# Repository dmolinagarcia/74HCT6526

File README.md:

>
> DISCLAIMER
> Everything you see here is the result of the work of an amateur hobbyist. I had no knowledge in any required field for this project when I started, so I offer no guarantee that, if you replicate my work, you may end burning up you Commodore, your fingertips, or your whole house.
> So far, no Commodore equipment (or fingertips, or whole house) have been permanently damaged in any way. But I can't promise to keep it that way.
>

# 74HCT6526 
The 74HCT6526 is a very amateur attempt at building a MOS6526 replica using discrete logic. This repo is publicly shared just for educational purposes, and I can offer no guarantee on the correct behaviour of this implementation. So far, it's working great for me, but I can't promise anything.

# Current Status
As of v0.2.2, the 74HCT6526 is extremely cycle accurate when compared to a real 6526. Some VICE test still fail on edge cases, but it has been tested against multiple games with very satisfactory results. 

# History
Work on the 74HCT6526 began in the summer of 2018. I was so impressed by other attempts at replicating Commodore chips, that I wanted to give it myself a try. I chose the CIA, as it wasn't replicated back then, even though it seemed the simplest chip. I had no previous knowledge in electronics, only some lessons back in college more than 20 years ago.

> ###### Important note
> Please visit http://forum.6502.org/viewtopic.php?f=4&t=5593 for more information

# Versioning
74HCT6526 is released under the following versioning scheme:

> MAJOR.MINOR.REVISION

For a stack to work properly, is mandatory that all boards share the same MAJOR.MINOR versión. Any change than renders a board incompatible with the previous releases triggers a new MINOR version. If a version only includes fixes, but does not alter the buses, it's only a new revision. There may be some cases where boards with different MAJOR.MINOR version can actually work together, but this is not something I can guarantee or predict. A deep look at the schematics to understand the differences between releases is needed to actually confirm this.

Under the current scheme, I don't think I'll ever need a new MAJOR version, but it is nice to have it there, just in case.

# Upgrades
In the upgrades folder, there's a guide for each version/board pair, with instructions to upgrade the board up until the latest version. You'll see theres no file for the latest version (As there's no upgrade path for it).

Whenever a new release is published, upgrade path for the now second-oldest release will by published.

> WARNING! I offer no guarantee on anything on this project, but, specially on the upgrades part. 

# Manufacturing
All boards are tested against JLCPCB and PCBWAY capabilities. For PCBWAY, there is no increase in cost compared to the standard 4 layer board.

# Releases
* v0.1.0  First production run. Only includes B0 (DDR and PORTs)
* v0.1.0a First production run for B1. (TIMERA and CREGA)
* v0.1.1  Second production run for B1. Fixes TASTART issue. First B2 (TIMERB and CREGB) 
* v0.1.2  First production run for B3. (SDR and ICR)
* v0.2.0  First MINOR advance. B0+B1+B2+B3 tested and validated. 
* v0.2.1  Fixes for Reload under Underflow issue. 
* v0.2.2  First production run for B4 (TOD). It now passes test 01 and 02 in both NEW and OLD modes.

# Changelog
## [0.2.2 ] - 23-Jun-2023
* B0. Some HCT parts are changed to HC
* B1. Split TIMER into modules for improved readability
* B2. Split TIMER into modules for improved readability
* B3. Issue #12. Fixed all issues for test 02
* B3. Master Switch for Mode Change. (Old vs NEW)
* B3. Some HC parts are changed to HCT
* B4. Added TOD PCB and SCH
* All boards. Published upgrade procedures

## [0.2.1 ] - 26-Mar-2023
* All boards. Added pdfs for all schematic and pcbs for all versions for ease of access
* B1. Changes to Reload portion of TimerA pipeline to fix 01cmpold issue
* B2. Changes to Reload portion of TimerA pipeline to fix 01cmpold issue
* B3. Added switch to select OLD or NEW CIA

## [0.2.0 ] - 24-Jan-2023
* All boards. Removed TARUNMODE from the ControlBus
* All boards. Updated for JLCPCB and PCBWAY capabilities
* All boards. Minor aesthetic changes to schematics
* All boards. Updated PDFs on the release
* B1. Optimized CNT edge detector
* B2. Optimized CNT edge detector
* B3. Fixed FLAG edge detector in ICR
* B3. Fixed SDR input and output issues from v0.1.2 (not sending nor receiving)

## [0.1.2 ] - 01-Nov-2022 
* B3. First release. SDR and ICR
* B2. Updates for JLCPCB capabilities
* All boards. Schematic review. Added /RES capacitor to prevent false restarts

## [0.1.1 ] - 24-Aug-2022 
* B2. First release. 
* B1. Fixed additional cycle on forceload by removing second flipflop in the chain (rolled-back)
* B1. Added additionad dFF to Start before being fed into the timer
* B1. D and DZ moved to separate buses on schematic.
* B0. Routing optimized. D and DZ moved to separate buses on schematic. Silkscreen improved. 

## [0.1.0a] - 06-Jun-2022
* B1 with TimerA and Control Register A. Ready for production. 

## [0.1.0 ] - 19-Oct-2021
* Mounting holes pads were covered with soldermask. Soldermask removed and pads properly labeled.
* Silkscreen fixes
* Updated gerber files
* B0 with DDRs, PORTs, and bus interface

# Status updates
* June 23, 2023. v0.2.2 released. Adds TOD (B4) and fixes more NEW to OLD issues. Now passes tests 01 and 02.
* March 26, 2023. v0.2.1 released. Fixes a missing IRQ issue on reload while underflowing. It also adds a selector for OLD vs NEW cia in ICR
* January 24, 2023. v0.2.0 released. Fixes a potential problem on B1 and B2 with CNT edge detector. It also fixes some bugs on B3. A cleanup of schematic, PCBs and PDFs for all boards has been done. TARUNMODE is removed from controlbus as it is not needed. This triggers a new MINOR version
* November 01, 2022. v0.1.2 released. Includes B3 (SDR+ICR) and some minor tweaks to all boards
* August 24, 2022. v0.1.1 released. Fixes a bug in B1 (TASTART) and adds B2. Minor routing fixes to all boards
* June 06, 2022. v0.1.0a released. It adds B1 to v0.1.0
* October 19, 2021. v0.1.0 is released. It add B0 to v0.1.0
* September 12th, 2021. Repository is now public. B0 schematic is 100% done. PCB layout is 100% done. It's currently being reviewed before sending it into production

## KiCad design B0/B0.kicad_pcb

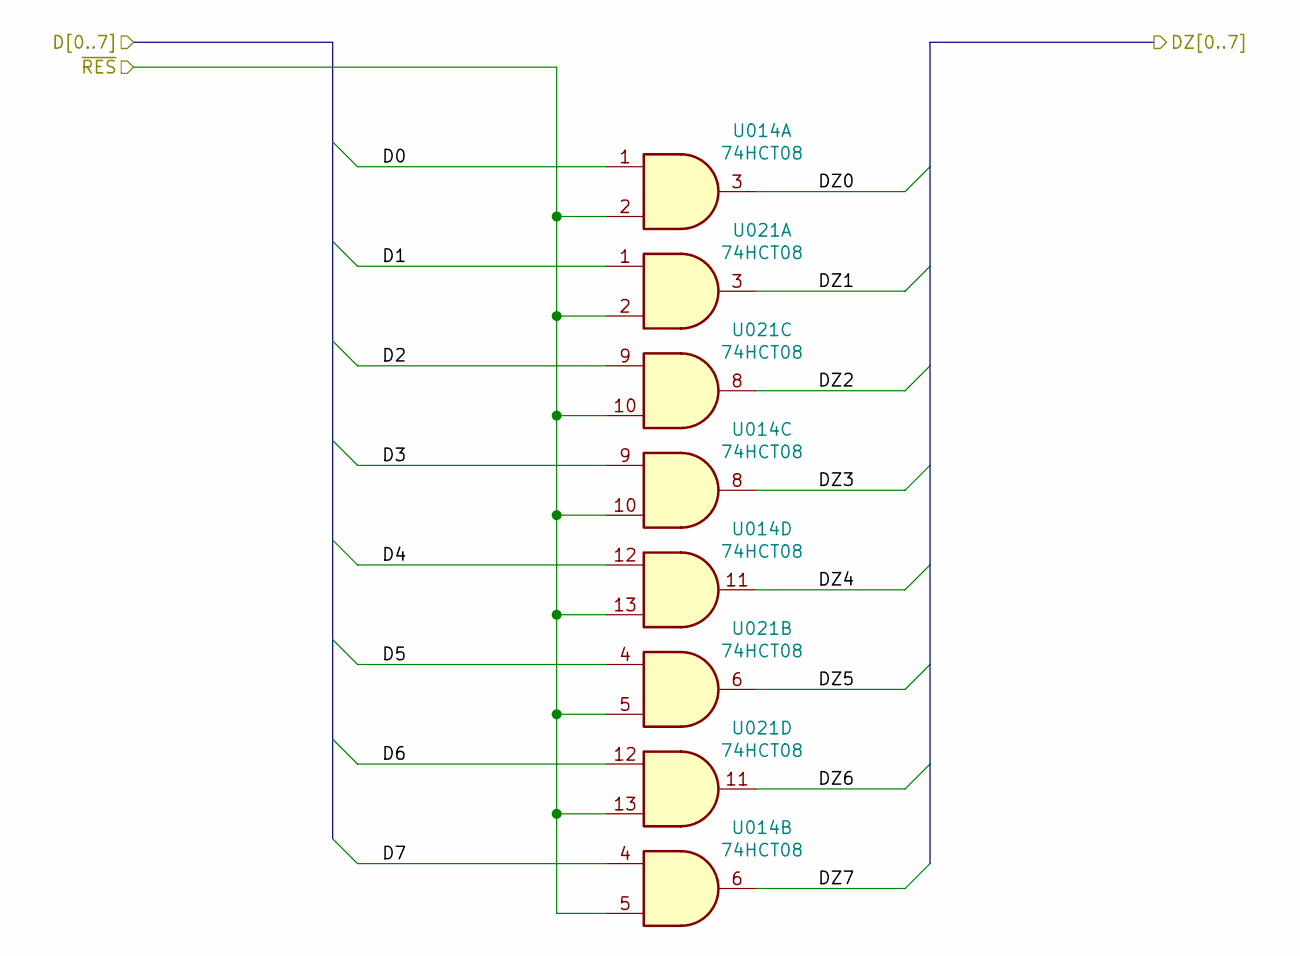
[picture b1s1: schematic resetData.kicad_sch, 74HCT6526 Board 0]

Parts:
U014, U021: 74HCT08; SO-14

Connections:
D0: U014.1; also elsewhere on the board
D1: U021.1; also elsewhere on the board
D2: U021.9; also elsewhere on the board
D3: U014.9; also elsewhere on the board
D4: U014.12; also elsewhere on the board
D5: U021.4; also elsewhere on the board
D6: U021.12; also elsewhere on the board
D7: U014.4; also elsewhere on the board
DZ0: U014.3; also elsewhere on the board
DZ1: U021.3; also elsewhere on the board
DZ2: U021.8; also elsewhere on the board
DZ3: U014.8; also elsewhere on the board
DZ4: U014.11; also elsewhere on the board
DZ5: U021.6; also elsewhere on the board
DZ6: U021.11; also elsewhere on the board
DZ7: U014.6; also elsewhere on the board
~RES: U014.2, U014.5, U014.10, U014.13, U021.2, U021.5, U021.10, U021.13; also elsewhere on the board

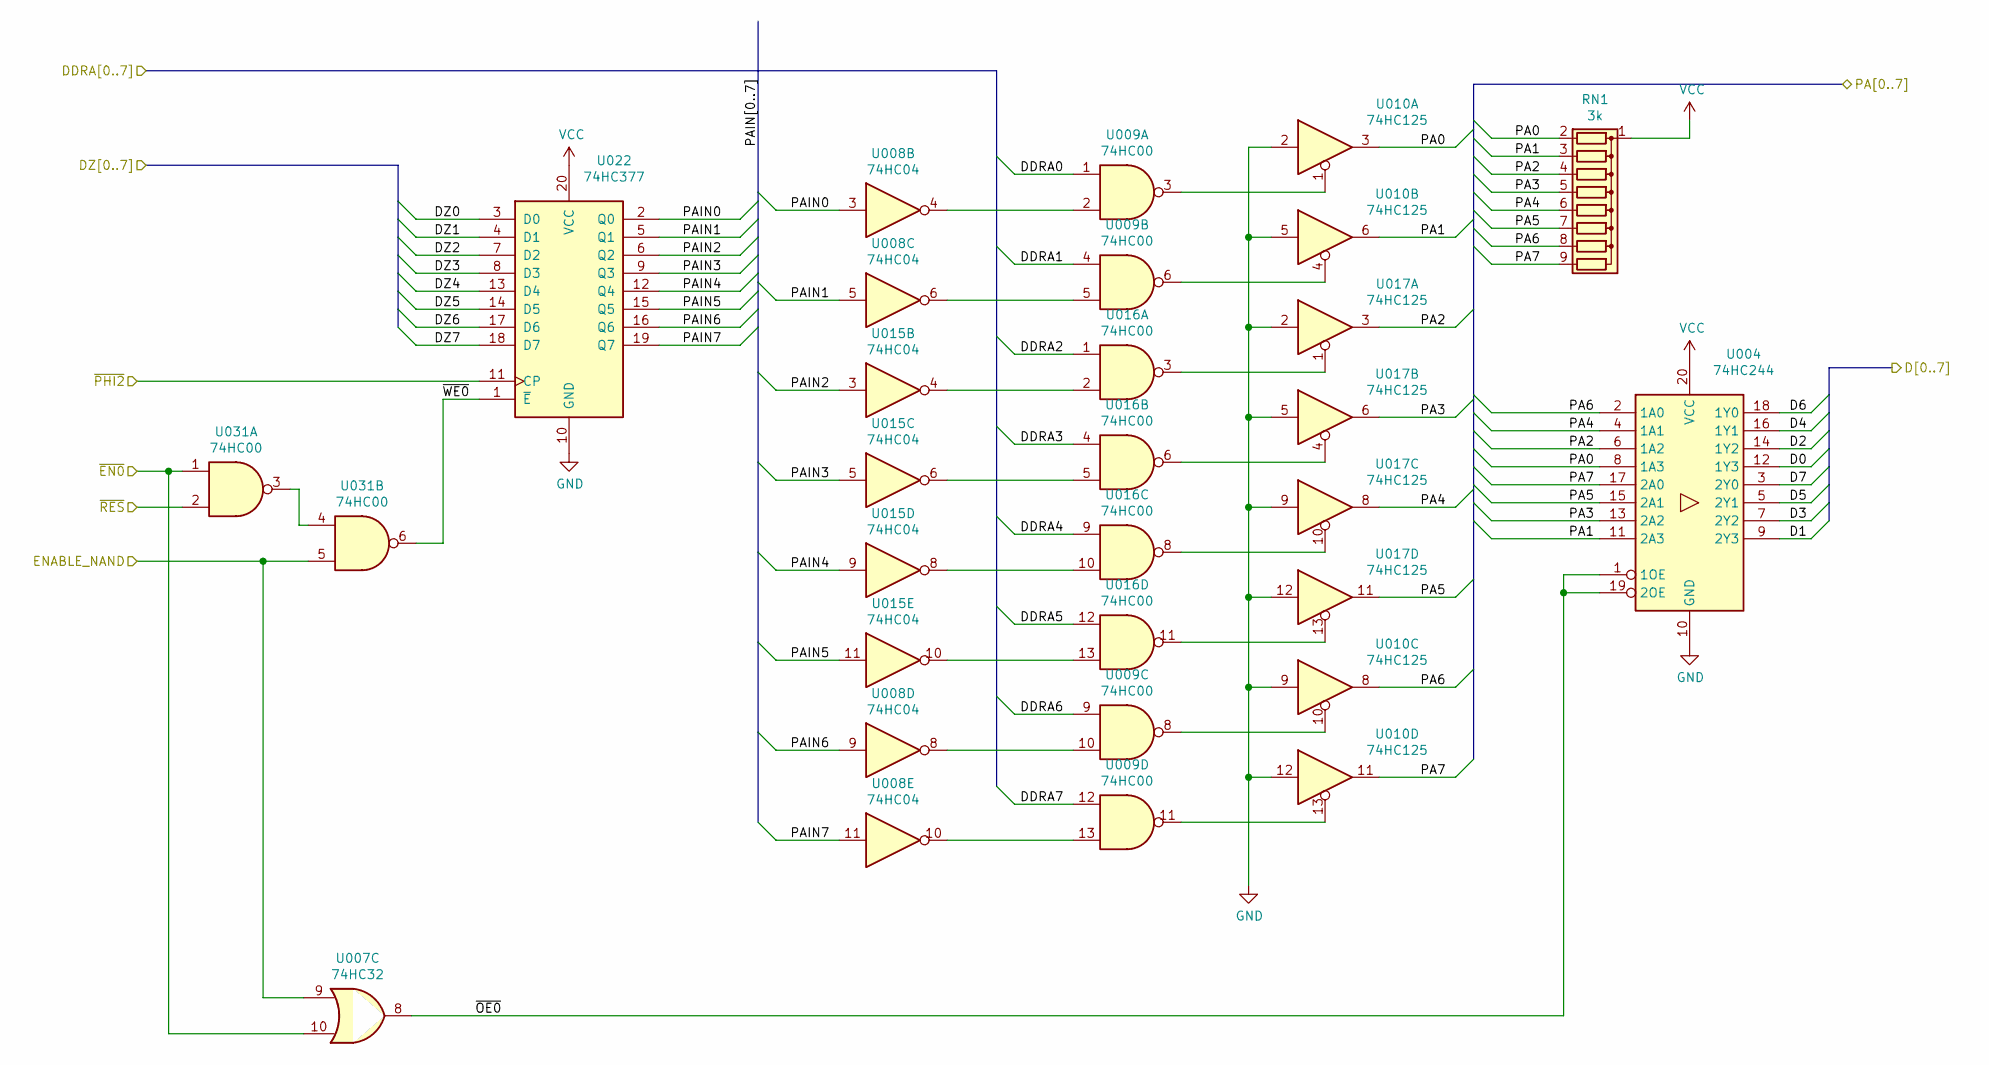
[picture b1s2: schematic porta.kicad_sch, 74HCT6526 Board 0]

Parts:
RN1: 3k; R_Array_SIP9
U004: 74HC244; SOIC-20W
U007: 74HC32; SO-14
U008, U015: 74HC04; SO-14
U009, U016, U031: 74HC00; SO-14
U010, U017: 74HC125; SO-14
U022: 74HC377; SOIC-20W

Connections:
/ddra/DDRA0: U009.1; also elsewhere on the board
/ddra/DDRA1: U009.4; also elsewhere on the board
/ddra/DDRA2: U016.1; also elsewhere on the board
/ddra/DDRA3: U016.4; also elsewhere on the board
/ddra/DDRA4: U016.9; also elsewhere on the board
/ddra/DDRA5: U016.12; also elsewhere on the board
/ddra/DDRA6: U009.9; also elsewhere on the board
/ddra/DDRA7: U009.12; also elsewhere on the board
/icInterface/PA0: RN1.2 (R1), U004.8 (1A3), U010.3; also elsewhere on the board
/icInterface/PA1: RN1.3 (R2), U004.11 (2A3), U010.6; also elsewhere on the board
/icInterface/PA2: RN1.4 (R3), U004.6 (1A2), U017.3; also elsewhere on the board
/icInterface/PA3: RN1.5 (R4), U004.13 (2A2), U017.6; also elsewhere on the board
/icInterface/PA4: RN1.6 (R5), U004.4 (1A1), U017.8; also elsewhere on the board
/icInterface/PA5: RN1.7 (R6), U004.15 (2A1), U017.11; also elsewhere on the board
/icInterface/PA6: RN1.8 (R7), U004.2 (1A0), U010.8; also elsewhere on the board
/icInterface/PA7: RN1.9 (R8), U004.17 (2A0), U010.11; also elsewhere on the board
/porta/PAIN0: U008.3, U022.2 (Q0)
/porta/PAIN1: U008.5, U022.5 (Q1)
/porta/PAIN2: U015.3, U022.6 (Q2)
/porta/PAIN3: U015.5, U022.9 (Q3)
/porta/PAIN4: U015.9, U022.12 (Q4)
/porta/PAIN5: U015.11, U022.15 (Q5)
/porta/PAIN6: U008.9, U022.16 (Q6)
/porta/PAIN7: U008.11, U022.19 (Q7)
/porta/~OE0: U004.1 (1OE), U004.19 (2OE), U007.8
/porta/~WE0: U022.1 (~E), U031.6
/~PHI2: U022.11 (CP); also elsewhere on the board
D0: U004.12 (1Y3); also elsewhere on the board
D1: U004.9 (2Y3); also elsewhere on the board
D2: U004.14 (1Y2); also elsewhere on the board
D3: U004.7 (2Y2); also elsewhere on the board
D4: U004.16 (1Y1); also elsewhere on the board
D5: U004.5 (2Y1); also elsewhere on the board
D6: U004.18 (1Y0); also elsewhere on the board
D7: U004.3 (2Y0); also elsewhere on the board
DZ0: U022.3 (D0); also elsewhere on the board
DZ1: U022.4 (D1); also elsewhere on the board
DZ2: U022.7 (D2); also elsewhere on the board
DZ3: U022.8 (D3); also elsewhere on the board
DZ4: U022.13 (D4); also elsewhere on the board
DZ5: U022.14 (D5); also elsewhere on the board
DZ6: U022.17 (D6); also elsewhere on the board
DZ7: U022.18 (D7); also elsewhere on the board
ENABLE_NAND: U007.9, U031.5; also elsewhere on the board
GND: U004.10 (GND), U010.2, U010.5, U010.9, U010.12, U017.2, U017.5, U017.9, U017.12, U022.10 (GND); also elsewhere on the board
unnamed: U008.4, U009.2
unnamed: U008.6, U009.5
unnamed: U008.8, U009.10
unnamed: U008.10, U009.13
unnamed: U009.3, U010.1
unnamed: U009.6, U010.4
unnamed: U009.8, U010.10
unnamed: U009.11, U010.13
unnamed: U015.4, U016.2
unnamed: U015.6, U016.5
unnamed: U015.8, U016.10
unnamed: U015.10, U016.13
unnamed: U016.3, U017.1
unnamed: U016.6, U017.4
unnamed: U016.8, U017.10
unnamed: U016.11, U017.13
unnamed: U031.3, U031.4
VCC: RN1.1 (common), U004.20 (VCC), U022.20 (VCC); also elsewhere on the board
~EN0: U007.10, U031.1; also elsewhere on the board
~RES: U031.2; also elsewhere on the board

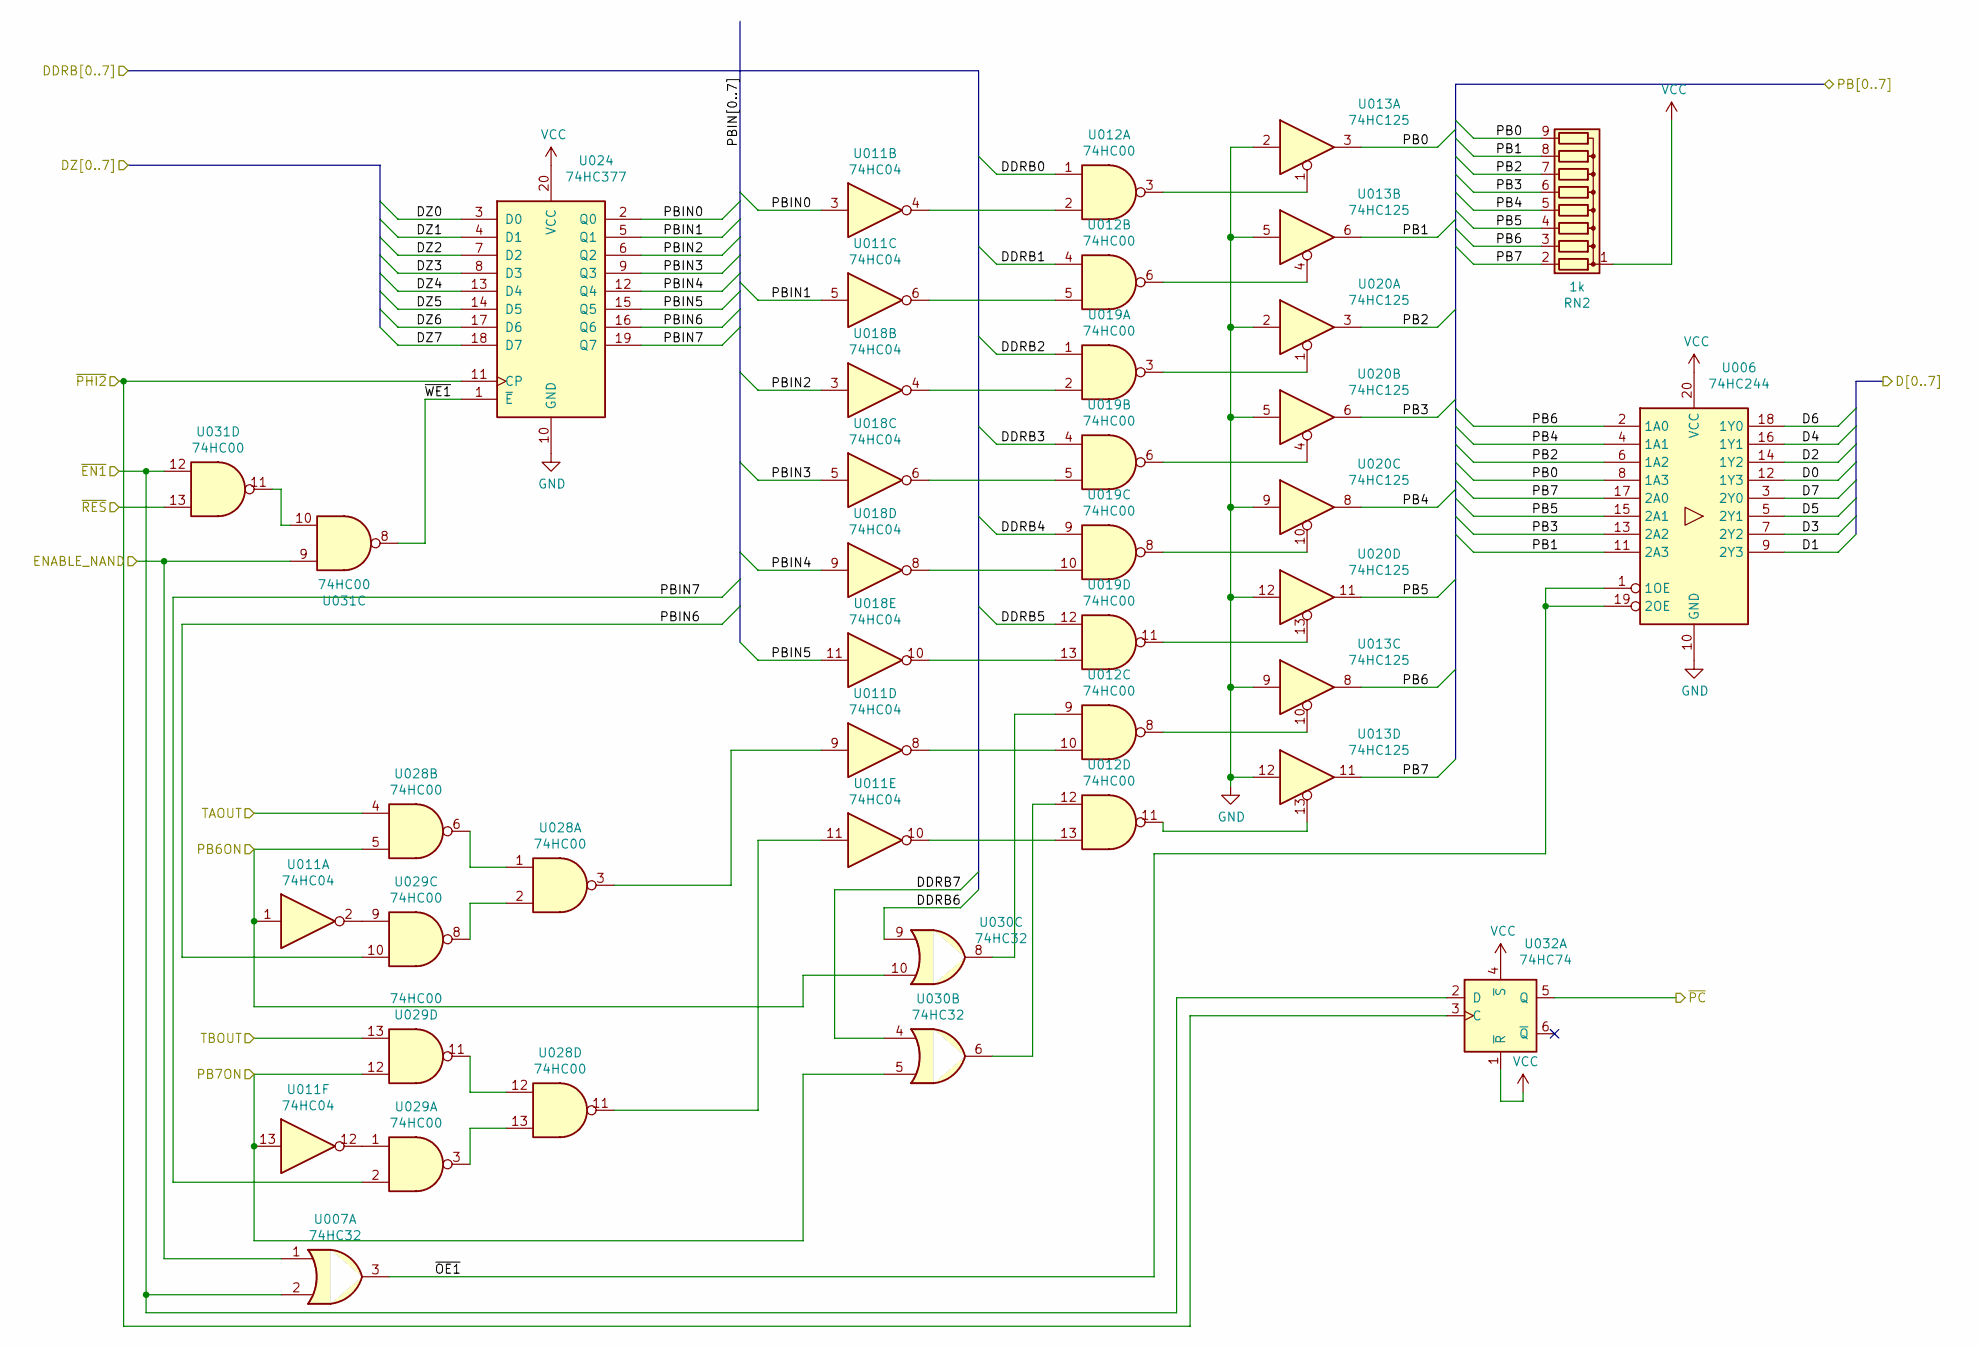
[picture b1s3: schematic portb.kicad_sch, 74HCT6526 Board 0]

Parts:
RN2: 1k; R_Array_SIP9
U006: 74HC244; SOIC-20W
U007, U030: 74HC32; SO-14
U011, U018: 74HC04; SO-14
U012, U019, U028, U029, U031: 74HC00; SO-14
U013, U020: 74HC125; SO-14
U024: 74HC377; SOIC-20W
U032: 74HC74; SO-14

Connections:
/ddrb/DDRB0: U012.1; also elsewhere on the board
/ddrb/DDRB1: U012.4; also elsewhere on the board
/ddrb/DDRB2: U019.1; also elsewhere on the board
/ddrb/DDRB3: U019.4; also elsewhere on the board
/ddrb/DDRB4: U019.9; also elsewhere on the board
/ddrb/DDRB5: U019.12; also elsewhere on the board
/ddrb/DDRB6: U030.9; also elsewhere on the board
/ddrb/DDRB7: U030.4; also elsewhere on the board
/icInterface/PB0: RN2.9 (R8), U006.8 (1A3), U013.3; also elsewhere on the board
/icInterface/PB1: RN2.8 (R7), U006.11 (2A3), U013.6; also elsewhere on the board
/icInterface/PB2: RN2.7 (R6), U006.6 (1A2), U020.3; also elsewhere on the board
/icInterface/PB3: RN2.6 (R5), U006.13 (2A2), U020.6; also elsewhere on the board
/icInterface/PB4: RN2.5 (R4), U006.4 (1A1), U020.8; also elsewhere on the board
/icInterface/PB5: RN2.4 (R3), U006.15 (2A1), U020.11; also elsewhere on the board
/icInterface/PB6: RN2.3 (R2), U006.2 (1A0), U013.8; also elsewhere on the board
/icInterface/PB7: RN2.2 (R1), U006.17 (2A0), U013.11; also elsewhere on the board
/icInterface/~PC: U032.5 (Q); also elsewhere on the board
/portb/PBIN0: U011.3, U024.2 (Q0)
/portb/PBIN1: U011.5, U024.5 (Q1)
/portb/PBIN2: U018.3, U024.6 (Q2)
/portb/PBIN3: U018.5, U024.9 (Q3)
/portb/PBIN4: U018.9, U024.12 (Q4)
/portb/PBIN5: U018.11, U024.15 (Q5)
/portb/PBIN6: U024.16 (Q6), U029.10
/portb/PBIN7: U024.19 (Q7), U029.2
/portb/~OE1: U006.1 (1OE), U006.19 (2OE), U007.3
/portb/~WE1: U024.1 (~E), U031.8
/~PHI2: U024.11 (CP), U032.3 (C); also elsewhere on the board
D0: U006.12 (1Y3); also elsewhere on the board
D1: U006.9 (2Y3); also elsewhere on the board
D2: U006.14 (1Y2); also elsewhere on the board
D3: U006.7 (2Y2); also elsewhere on the board
D4: U006.16 (1Y1); also elsewhere on the board
D5: U006.5 (2Y1); also elsewhere on the board
D6: U006.18 (1Y0); also elsewhere on the board
D7: U006.3 (2Y0); also elsewhere on the board
DZ0: U024.3 (D0); also elsewhere on the board
DZ1: U024.4 (D1); also elsewhere on the board
DZ2: U024.7 (D2); also elsewhere on the board
DZ3: U024.8 (D3); also elsewhere on the board
DZ4: U024.13 (D4); also elsewhere on the board
DZ5: U024.14 (D5); also elsewhere on the board
DZ6: U024.17 (D6); also elsewhere on the board
DZ7: U024.18 (D7); also elsewhere on the board
ENABLE_NAND: U007.1, U031.9; also elsewhere on the board
GND: U006.10 (GND), U013.2, U013.5, U013.9, U013.12, U020.2, U020.5, U020.9, U020.12, U024.10 (GND); also elsewhere on the board
unnamed: U011.2, U029.9
unnamed: U011.4, U012.2
unnamed: U011.6, U012.5
unnamed: U011.8, U012.10
unnamed: U011.9, U028.3
unnamed: U011.10, U012.13
unnamed: U011.11, U028.11
unnamed: U011.12, U029.1
unnamed: U012.3, U013.1
unnamed: U012.6, U013.4
unnamed: U012.8, U013.10
unnamed: U012.9, U030.8
unnamed: U012.11, U013.13
unnamed: U012.12, U030.6
unnamed: U018.4, U019.2
unnamed: U018.6, U019.5
unnamed: U018.8, U019.10
unnamed: U018.10, U019.13
unnamed: U019.3, U020.1
unnamed: U019.6, U020.4
unnamed: U019.8, U020.10
unnamed: U019.11, U020.13
unnamed: U028.1, U028.6
unnamed: U028.2, U029.8
unnamed: U028.12, U029.11
unnamed: U028.13, U029.3
unnamed: U031.10, U031.11
PB6ON: U011.1, U028.5, U030.10; also elsewhere on the board
PB7ON: U011.13, U029.12, U030.5; also elsewhere on the board
TAOUT: U028.4; also elsewhere on the board
TBOUT: U029.13; also elsewhere on the board
VCC: RN2.1 (common), U006.20 (VCC), U024.20 (VCC), U032.1 (~R), U032.4 (~S); also elsewhere on the board
~EN1: U007.2, U031.12, U032.2 (D); also elsewhere on the board
~RES: U031.13; also elsewhere on the board

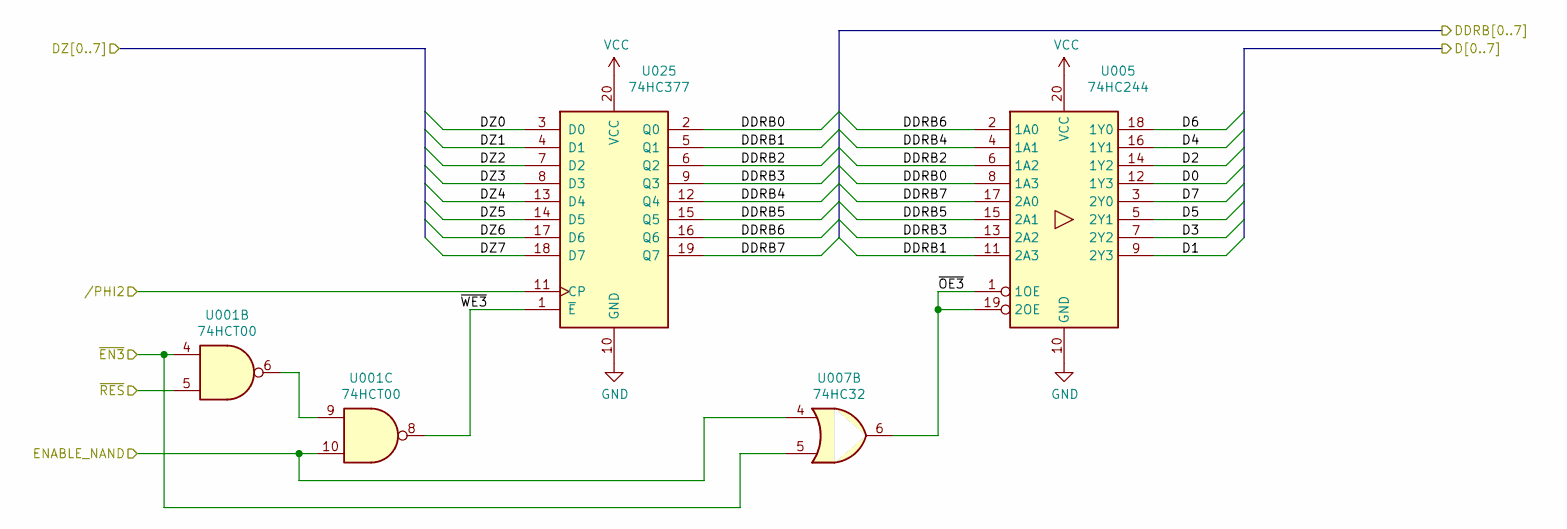
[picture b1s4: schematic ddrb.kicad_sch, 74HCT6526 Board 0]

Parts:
U001: 74HCT00; SO-14
U005: 74HC244; SOIC-20W
U007: 74HC32; SO-14
U025: 74HC377; SOIC-20W

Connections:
/ddrb/DDRB0: U005.8 (1A3), U025.2 (Q0); also elsewhere on the board
/ddrb/DDRB1: U005.11 (2A3), U025.5 (Q1); also elsewhere on the board
/ddrb/DDRB2: U005.6 (1A2), U025.6 (Q2); also elsewhere on the board
/ddrb/DDRB3: U005.13 (2A2), U025.9 (Q3); also elsewhere on the board
/ddrb/DDRB4: U005.4 (1A1), U025.12 (Q4); also elsewhere on the board
/ddrb/DDRB5: U005.15 (2A1), U025.15 (Q5); also elsewhere on the board
/ddrb/DDRB6: U005.2 (1A0), U025.16 (Q6); also elsewhere on the board
/ddrb/DDRB7: U005.17 (2A0), U025.19 (Q7); also elsewhere on the board
/ddrb/~OE3: U005.1 (1OE), U005.19 (2OE), U007.6
/ddrb/~WE3: U001.8, U025.1 (~E)
/~PHI2: U025.11 (CP); also elsewhere on the board
D0: U005.12 (1Y3); also elsewhere on the board
D1: U005.9 (2Y3); also elsewhere on the board
D2: U005.14 (1Y2); also elsewhere on the board
D3: U005.7 (2Y2); also elsewhere on the board
D4: U005.16 (1Y1); also elsewhere on the board
D5: U005.5 (2Y1); also elsewhere on the board
D6: U005.18 (1Y0); also elsewhere on the board
D7: U005.3 (2Y0); also elsewhere on the board
DZ0: U025.3 (D0); also elsewhere on the board
DZ1: U025.4 (D1); also elsewhere on the board
DZ2: U025.7 (D2); also elsewhere on the board
DZ3: U025.8 (D3); also elsewhere on the board
DZ4: U025.13 (D4); also elsewhere on the board
DZ5: U025.14 (D5); also elsewhere on the board
DZ6: U025.17 (D6); also elsewhere on the board
DZ7: U025.18 (D7); also elsewhere on the board
ENABLE_NAND: U001.10, U007.4; also elsewhere on the board
GND: U005.10 (GND), U025.10 (GND); also elsewhere on the board
unnamed: U001.6, U001.9
VCC: U005.20 (VCC), U025.20 (VCC); also elsewhere on the board
~EN3: U001.4, U007.5; also elsewhere on the board
~RES: U001.5; also elsewhere on the board

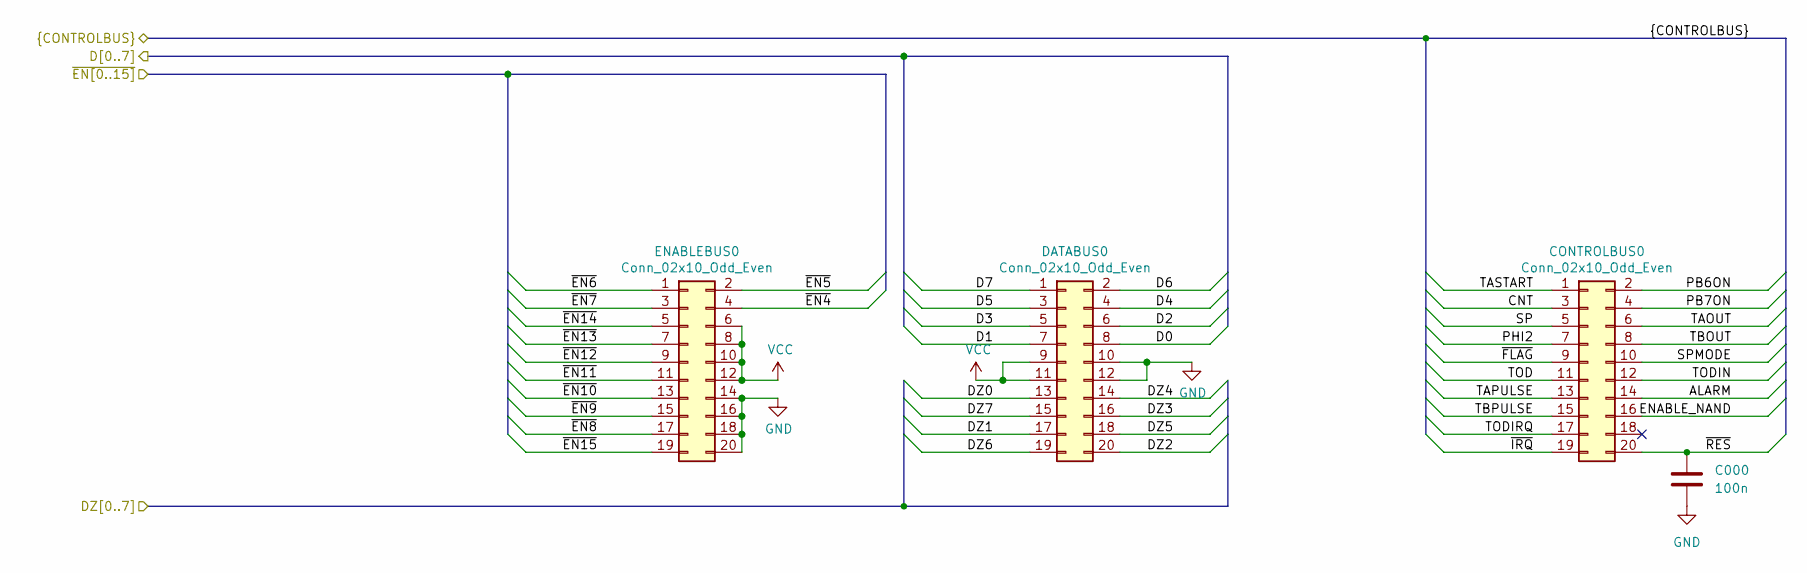
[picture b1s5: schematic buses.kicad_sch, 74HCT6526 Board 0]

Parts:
C000: 100n; C_0603_1608Metric
CONTROLBUS0: Conn_02x10_Odd_Even; PinHeader_2x10_P2.54mm_Vertical
DATABUS0: Conn_02x10_Odd_Even; PinHeader_2x10_P2.54mm_Vertical
ENABLEBUS0: Conn_02x10_Odd_Even; PinHeader_2x10_P2.54mm_Vertical

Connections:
ALARM: CONTROLBUS0.14
CNT: CONTROLBUS0.3; also elsewhere on the board
D0: DATABUS0.8; also elsewhere on the board
D1: DATABUS0.7; also elsewhere on the board
D2: DATABUS0.6; also elsewhere on the board
D3: DATABUS0.5; also elsewhere on the board
D4: DATABUS0.4; also elsewhere on the board
D5: DATABUS0.3; also elsewhere on the board
D6: DATABUS0.2; also elsewhere on the board
D7: DATABUS0.1; also elsewhere on the board
DZ0: DATABUS0.13; also elsewhere on the board
DZ1: DATABUS0.17; also elsewhere on the board
DZ2: DATABUS0.20; also elsewhere on the board
DZ3: DATABUS0.16; also elsewhere on the board
DZ4: DATABUS0.14; also elsewhere on the board
DZ5: DATABUS0.18; also elsewhere on the board
DZ6: DATABUS0.19; also elsewhere on the board
DZ7: DATABUS0.15; also elsewhere on the board
ENABLE_NAND: CONTROLBUS0.16; also elsewhere on the board
GND: C000.2, DATABUS0.10, DATABUS0.12, ENABLEBUS0.14, ENABLEBUS0.16, ENABLEBUS0.18, ENABLEBUS0.20; also elsewhere on the board
PB6ON: CONTROLBUS0.2; also elsewhere on the board
PB7ON: CONTROLBUS0.4; also elsewhere on the board
PHI2: CONTROLBUS0.7; also elsewhere on the board
SP: CONTROLBUS0.5; also elsewhere on the board
SPMODE: CONTROLBUS0.10
TAOUT: CONTROLBUS0.6; also elsewhere on the board
TAPULSE: CONTROLBUS0.13
TASTART: CONTROLBUS0.1
TBOUT: CONTROLBUS0.8; also elsewhere on the board
TBPULSE: CONTROLBUS0.15
TOD: CONTROLBUS0.11; also elsewhere on the board
TODIN: CONTROLBUS0.12
TODIRQ: CONTROLBUS0.17
VCC: DATABUS0.9, DATABUS0.11, ENABLEBUS0.6, ENABLEBUS0.8, ENABLEBUS0.10, ENABLEBUS0.12; also elsewhere on the board
~EN4: ENABLEBUS0.4; also elsewhere on the board
~EN5: ENABLEBUS0.2; also elsewhere on the board
~EN6: ENABLEBUS0.1; also elsewhere on the board
~EN7: ENABLEBUS0.3; also elsewhere on the board
~EN8: ENABLEBUS0.17; also elsewhere on the board
~EN9: ENABLEBUS0.15; also elsewhere on the board
~EN10: ENABLEBUS0.13; also elsewhere on the board
~EN11: ENABLEBUS0.11; also elsewhere on the board
~EN12: ENABLEBUS0.9; also elsewhere on the board
~EN13: ENABLEBUS0.7; also elsewhere on the board
~EN14: ENABLEBUS0.5; also elsewhere on the board
~EN15: ENABLEBUS0.19; also elsewhere on the board
~FLAG: CONTROLBUS0.9; also elsewhere on the board
~IRQ: CONTROLBUS0.19; also elsewhere on the board
~RES: C000.1, CONTROLBUS0.20; also elsewhere on the board

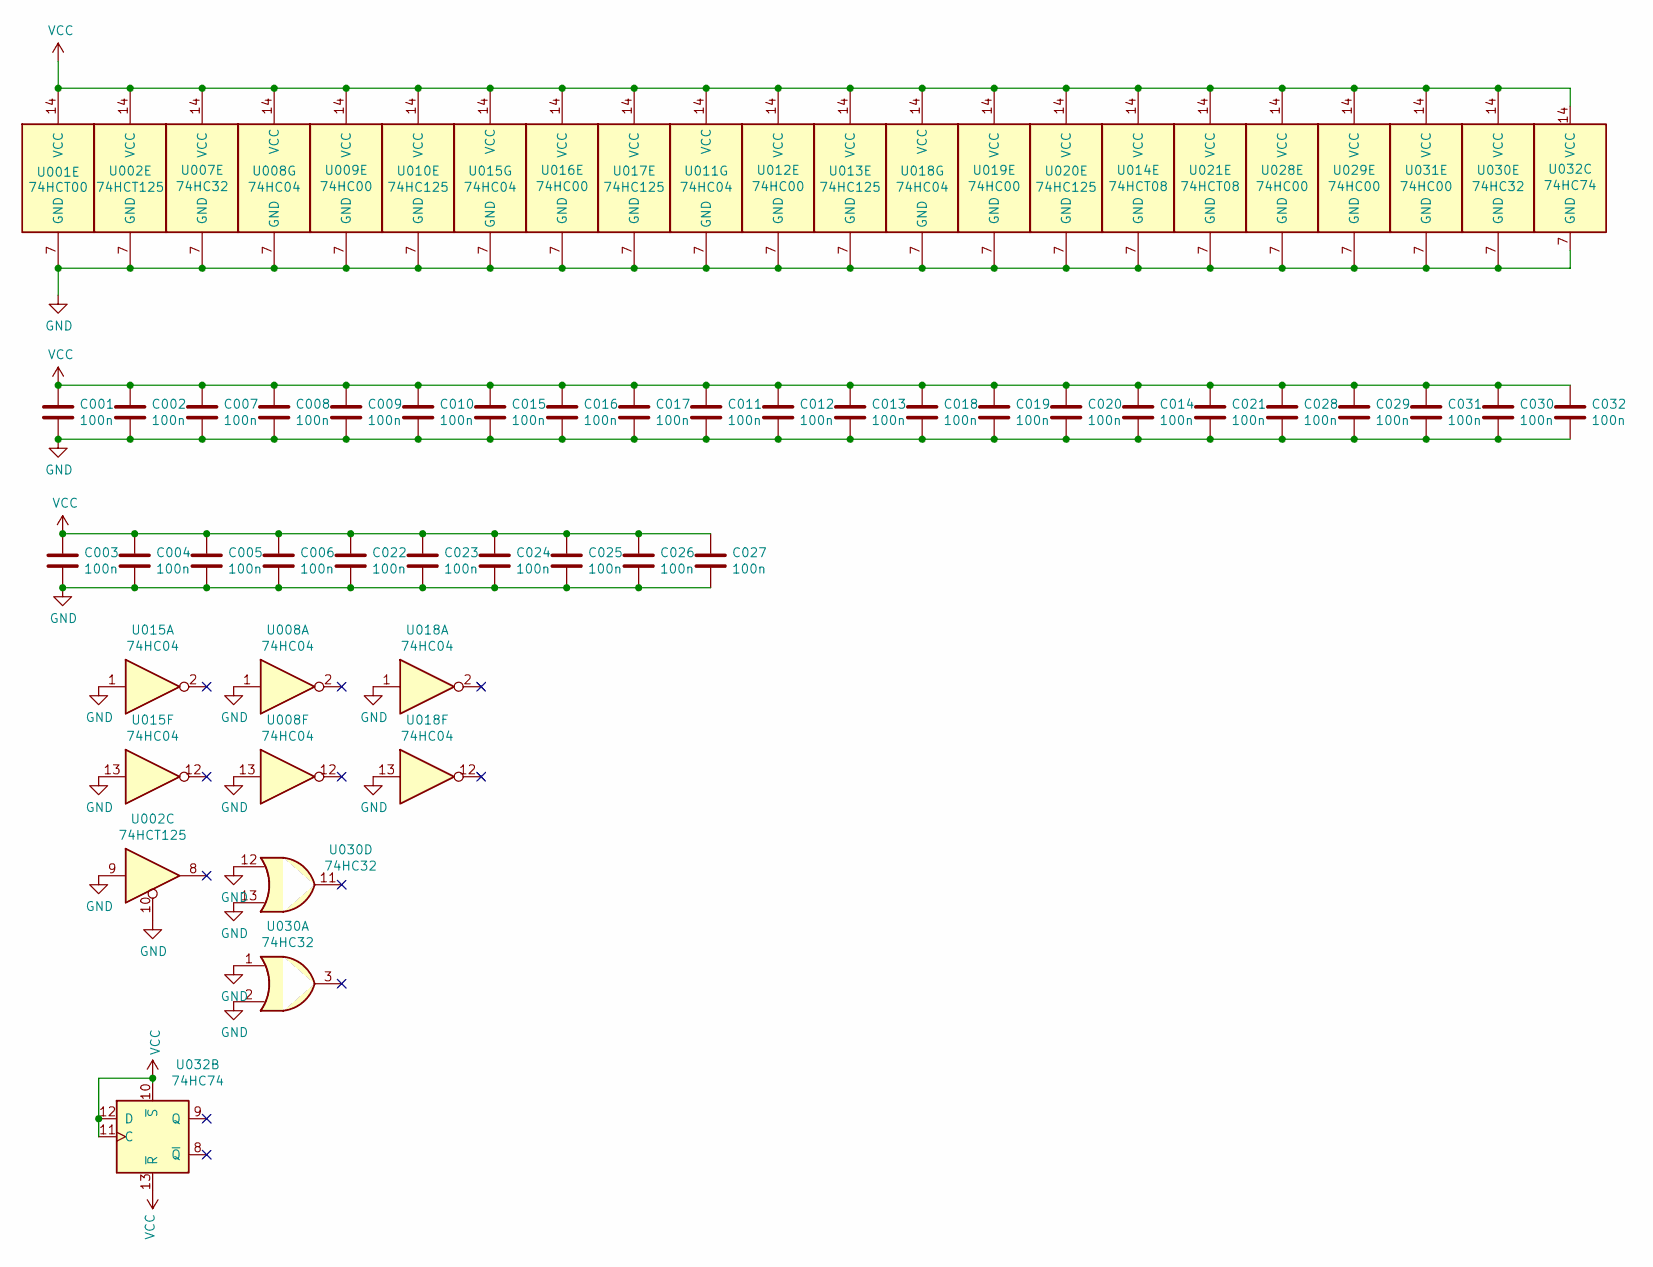
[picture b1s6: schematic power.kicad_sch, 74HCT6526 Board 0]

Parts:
C001, C002, C003, C004, C005, C006, C007, C008, C009, C010, C011, C012, C013, C014, C015, C016, C017, C018, C019, C020, C021, C022, C023, C024, C025, C026, C027, C028, C029, C030, C031, C032: 100n; 0603_SMD
U001: 74HCT00; SO-14
U002: 74HCT125; SO-14
U007, U030: 74HC32; SO-14
U008, U011, U015, U018: 74HC04; SO-14
U009, U012, U016, U019, U028, U029, U031: 74HC00; SO-14
U010, U013, U017, U020: 74HC125; SO-14
U014, U021: 74HCT08; SO-14
U032: 74HC74; SO-14

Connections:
GND: C001.2, C002.2, C003.2, C004.2, C005.2, C006.2, C007.2, C008.2, C009.2, C010.2, C011.2, C012.2, C013.2, C014.2, C015.2, C016.2, C017.2, C018.2, C019.2, C020.2, C021.2, C022.2, C023.2, C024.2, C025.2, C026.2, C027.2, C028.2, C029.2, C030.2, C031.2, C032.2, U001.7 (GND), U002.7 (GND), U002.9, U002.10, U007.7 (GND), U008.1, U008.7 (GND), U008.13, U009.7 (GND), U010.7 (GND), U011.7 (GND), U012.7 (GND), U013.7 (GND), U014.7 (GND), U015.1, U015.7 (GND), U015.13, U016.7 (GND), U017.7 (GND), U018.1, U018.7 (GND), U018.13, U019.7 (GND), U020.7 (GND), U021.7 (GND), U028.7 (GND), U029.7 (GND), U030.1, U030.2, U030.7 (GND), U030.12, U030.13, U031.7 (GND), U032.7 (GND); also elsewhere on the board
VCC: C001.1, C002.1, C003.1, C004.1, C005.1, C006.1, C007.1, C008.1, C009.1, C010.1, C011.1, C012.1, C013.1, C014.1, C015.1, C016.1, C017.1, C018.1, C019.1, C020.1, C021.1, C022.1, C023.1, C024.1, C025.1, C026.1, C027.1, C028.1, C029.1, C030.1, C031.1, C032.1, U001.14 (VCC), U002.14 (VCC), U007.14 (VCC), U008.14 (VCC), U009.14 (VCC), U010.14 (VCC), U011.14 (VCC), U012.14 (VCC), U013.14 (VCC), U014.14 (VCC), U015.14 (VCC), U016.14 (VCC), U017.14 (VCC), U018.14 (VCC), U019.14 (VCC), U020.14 (VCC), U021.14 (VCC), U028.14 (VCC), U029.14 (VCC), U030.14 (VCC), U031.14 (VCC), U032.10 (~S), U032.11 (C), U032.12 (D), U032.13 (~R), U032.14 (VCC); also elsewhere on the board

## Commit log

2021-09-12 Fix typo in 74HCT6526.kicad_sch
2021-10-02 v0.1
    B0 v0.1 Production release
    B1 N/A
    B2 N/A
    B3 N/A
    B4 N/A
2021-10-17 Added gerber for v0.1.1
2021-10-18 Fixed Soldermask over mount pads
2021-10-18 Fixed mounted pads thermal relief
2021-10-19 v0.1.0 completed
2022-03-20 B1 CREGA added
    Work started on b1. CREGA added.
    Minor changes to B0 schematic properties.
2022-04-27 v0.1.0 B1 uploaded
    Pending review and production. Version release will be published once sent for fab
2022-05-10 Fixed CREGA Clock
    Fixed CREGA Clock
2022-06-06 B1 into production!
2022-07-30 Pre B2 Clone
2022-08-13 B2 almost ready
2022-08-17 Almost 0.1.1
2022-08-24 B2 Ready for prod
2022-09-02 Gerbers B2 and B1
2022-09-12 Updates to B3
2022-09-23 B3 added. First revision
    Still not verified.
2022-09-24 Added ICR. B2 fixes
2022-11-01 Release v0.1.2. Added SDR!
2022-11-30 Fixed B3 3d footprints
2023-01-23 B0 ready for v0.2.0 release.
2023-01-23 B1 ready for v0.2.0 release
2023-01-24 B2 ready for v0.2.0 release
2023-01-24 B3 ready for v0.2.0 release
2023-01-24 Ready for release 0.2.0
2023-02-05 LA test from 01cmp bug added
2023-02-05 Update to readme.
2023-02-13 01cmp test data
2023-02-15 Added PDFs for all versions
2023-03-26 Ready for v0.2.1
2023-03-26 Update to readme
2023-04-20 B2 refactored. B4 Added. TOD sch completed.
2023-05-02 TOD is here
2023-05-02 Issue #12 diagnosis
2023-05-07 Fixing ICR
2023-06-23 Ready for v0.2.2
2023-11-01 .gitignore
2023-11-01 Update B3_v0.1.2.md
    Update B3_v0.1.2.md for scratch build
2023-11-07 Fixed B3 v0.1.2 Upgrade
2023-11-08 Upgrades to the upgrades :)
